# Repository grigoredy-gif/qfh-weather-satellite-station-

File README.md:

# QFH weather-satellite station: my own antenna and an all-discrete receiver

I'm Edy Grigore, an Electrical Engineering student at the University of
Twente. This is my personal project to receive weather satellites on 137 MHz
with hardware I designed myself: a QFH antenna and a radio receiver built only
from discrete parts (transistors, diodes, inductors and capacitors, no chips
in the signal path).

*Receiver version 2. This is a 3D picture that KiCad draws from the board file,
not a photo. The boards were ordered on 16 November 2026 and have not arrived
yet.*

Each section below starts with a short explanation that needs no radio
background. The numbers and the reasoning follow, with links to the detailed
pages. Words like "IF" or "image" are explained in
[Words used on this page](#words-used-on-this-page).

## Where the project stands (16 November 2026)

| Part | State |
|---|---|
| The antenna | designed with my own MATLAB tool, built and measured |
| Listening with a bought radio (SDR) | the Meteor-M satellite signal received and recognised; no picture decoded, because the signal was too weak |
| Receiver version 1 | designed, simulated and laid out; never ordered, because it was too expensive to have assembled |
| Receiver version 2 | designed, simulated block by block, laid out and checked. **Ordered on 16 November 2026: 5 boards, 2 of them assembled by JLCPCB. Not delivered yet, not tested, nothing measured** |

## Why I'm doing this

In my first year, the Module 4 project was to design an antenna and a
transmitter PCB. I really enjoyed that field, together with the High Frequency
Electronics, Electromagnetostatics and Electrodynamics courses, so I wanted to
go deeper: design my own antenna and my own receiver, and do the receiver fully
analog so I have to understand every stage at component level.

## How a weather picture reaches the ground

A weather satellite sends its pictures as a radio signal near 137 MHz. On the
ground the signal is extremely weak: around −90 to −100 dBm from my antenna,
which is less than a billionth of a milliwatt, or a few microvolts. The
receiver amplifies it to about a volt, filters out everything else, and turns
it into sound: a 2400 Hz tone whose loudness follows the brightness of the
picture, line by line. In my design an ESP32 microcontroller samples that
tone, and software on a PC turns it back into the picture (that firmware is
not written yet).

That is how the analog NOAA satellites worked (their "APT" signal). They were
switched off in 2025. The Meteor-M satellites that are still up send a digital
signal ("LRPT") that an analog FM receiver like mine cannot decode. So I test
the two halves separately: the antenna with a bought SDR on Meteor-M, and my
receiver on the bench, with a recorded NOAA pass played back into it by an
ADALM-Pluto SDR.

## The project in four parts

### 1. The antenna

A QFH (quadrifilar helix) antenna is two wire loops twisted around a mast. It
receives the circularly polarised signal of a satellite from almost anywhere
in the sky, so it does not need to be pointed. I wrote a MATLAB tool that
computes the antenna, exports it for simulation in NEC2, and prints a drilling
template for the mast. Then I built the antenna and measured it.

*Photo of my receiving setup in a park: the QFH antenna on its mast on a
concrete post, the ADALM-Pluto SDR (the blue box) and the laptop. The laptop
screen is edited in: it shows a SatDump screenshot from my own recording of
5 August 2026 (the spectrum and waterfall at 137.9 MHz). When the photo was
taken, the laptop showed a document.*

| The model (MATLAB) | The built antenna, measured |
|---|---|
|  |  |

*Left: the antenna as my MATLAB tool draws it (137.5 MHz, 1.78 mm wire).
Right: a measurement with a miniVNA Tiny (26 July 2026), S11 in dB in blue:
the best match is about −15 dB near 133 MHz and about −10 dB at 137.5 MHz.*

The built antenna resonates about 3 % lower than designed. For receiving, that
costs about 0.5 dB. **Deeper:** [`qfh_matlab/`](qfh_matlab) has the tool, the
4nec2 simulation next to this measurement, and why the plain design formulas
come out 2.2 % low in NEC2. The toolchain reproduces its reference program
exactly (all 127 NEC wire cards identical).

### 2. Listening with a bought SDR

Before building my own receiver, I recorded Meteor-M passes with the antenna
and an ADALM-Pluto. The signal is there (picture below), and SatDump's
decoder locked onto its error-correcting code, but no picture ever came out.

*Measurement: a real recording of Meteor-M N2-3 on 137.9 MHz, 6 August 2026,
shown by my `baseband_check.m`. Time runs upwards; the satellite's signal is
the band about 110 kHz wide in the middle.*

I first suspected the satellite. With help from the r/meteorsatellites
community I found the real cause: the mean signal-to-noise ratio was only
about 1.8 dB, below the 3 to 4 dB the decoder needs. The Pluto has no filter
and no low-noise amplifier at its input. **Deeper:**
[`lrpt_decoder/`](lrpt_decoder) (my own analysis chain, and the correction of
my first conclusion) and [`baseband_tools/`](baseband_tools) (tools that check
a recording before decoding it).

### 3. Receiver version 1: one conversion, coils wound by hand

The receiver is a superheterodyne. It mixes the 137.9 MHz signal with a
125 MHz signal made on the board, which shifts it down to 12.9 MHz (the
"intermediate frequency", IF). At 12.9 MHz it is much easier to amplify and
filter. Four amplifier stages give about 96 dB of gain there, a limiter cuts
the signal to a constant size, and a slope detector turns the frequency
changes into the 2400 Hz tone.

*Version 1, KiCad 3D picture (not a photo): 210 × 75 mm, 205 parts.*

I simulated every block in LTspice, then the whole receiver, and laid out the
board. It was checked many times. But building it needs 11 coils wound by hand
(7 on toroid cores, 4 air coils) and 11 trimmer capacitors that have to be
adjusted on the bench. JLCPCB quoted about €140 to assemble two boards. And
96 dB of gain at one frequency is easy to turn into an oscillator by
accident: the board had to grow to 210 mm with two shield fences across it.
I never ordered it.

**Deeper:** [`fm_receiver/`](fm_receiver) (the circuit and its 13
simulations) and [`pcb/`](pcb) (the board, every issue found and fixed).

### 4. Receiver version 2: two conversions, nothing to wind or tune

Version 2 does the same job, but it is designed for a factory. It has no coils
to wind and no trimmers to turn. JLCPCB places all 252 surface-mount parts by
machine and also solders the three connectors.

*Version 2 from above (KiCad 3D picture, not a photo): 100 × 100 mm. The
signal enters at the SMA jack at the top left, runs along the top edge, down
the right side, and back to the left through the second IF. The ESP32 DevKitC
plugs into the two socket rows at the bottom.*

Without trimmers, every tuned circuit has to be wide enough that normal part
tolerances cannot push it off the signal. At 12.9 MHz a filter that wide lets
through far too much noise. So version 2 converts the signal a second time,
from 12.9 MHz down to 1.418 MHz, where a filter of the right width (131 kHz)
is still tolerant enough. That second conversion is the central idea of
version 2. **Deeper:** [`fm_receiver_v2/`](fm_receiver_v2) and the board in
[`pcb_v2/`](pcb_v2).

## From version 1 to version 2

| | Version 1 | Version 2 |
|---|---|---|
| Conversions | one: 137.9 → 12.9 MHz | two: 137.9 → 12.9 → 1.418 MHz |
| Where the gain is | about 96 dB in one strip at 12.9 MHz | split between 12.9 MHz and 1.418 MHz |
| Coils | 11, wound by hand | 11 small SMD inductors, 3 values |
| Trimmers | 11, adjusted by hand | none |
| Oscillators | 25 MHz crystal × 5 = 125 MHz | the same, plus a 14.31818 MHz crystal |
| FM detector | slope detector (a tuned circuit) | charge-pump detector (no tuned circuit) |
| Supply | the ESP32 board's "5 V" pin (really about 4.6 V) | 3.3 V from a discrete regulator |
| Transistors | 20 | 38 |
| Parts | 205 | 252 surface-mount parts and 3 through-hole connectors |
| Board | 210 × 75 mm, 2 layers | 100 × 100 mm, 2 layers, all parts on the top |
| Assembly | by hand (JLCPCB quoted about €140 for 2 boards) | by JLCPCB: $39.99 (about €36) for 5 boards, 2 of them assembled |
| State | complete design, never ordered | ordered on 16 November 2026, not delivered yet |

The rule of the project stays the same: no ICs in the signal path. **Deeper:**
the reasons for each change are in
[`fm_receiver_v2/DESIGN_LOG.md`](fm_receiver_v2/DESIGN_LOG.md) ("Why a second
version" and "Frequency plan").

## Cost

**In short:** having two boards of version 1 assembled by JLCPCB was quoted at
about €140. Version 2 was ordered for $39.99 (about €36): five boards, two of
them assembled. The saving does not come from cheaper transistors. It comes
from designing the receiver around the way the factory charges.

| What | Price | Kind of figure | Source |
|---|---|---|---|
| Version 1, 2 boards assembled by JLCPCB (7 Nov 2026) | about €140 | JLCPCB quote | [`pcb/DESIGN_LOG.md`](pcb/DESIGN_LOG.md) |
| Version 2, first try with the wrong surface finish (OSP), 14 Nov | €143.52 for the assembly + €8.42 for the boards | JLCPCB quote | [`READ_ME_FIRST.txt`](pcb_v2/fabrication/READ_ME_FIRST.txt) |
| Version 2 without the connectors, my computation from JLCPCB's fee table, 14 Nov | $41.06 = €37.2 | computed | [`PARTS.md`](fm_receiver_v2/PARTS.md) |
| Version 2 in the cart, without the connectors: 5 boards, 2 assembled, HASL finish, 14 Nov | €3.62 + €30.37 = €33.99 | JLCPCB cart | [`COST.md`](fm_receiver_v2/COST.md) |
| **Version 2, ordered 16 Nov: 5 boards, 2 assembled with the connectors** | **$3.63 + $36.36 = $39.99 (about €36)** | **JLCPCB order list** | [`COST.md`](fm_receiver_v2/COST.md) |

All figures are without shipping, tax and the ESP32 board. The dollar figure is
about €36 at €1 = $1.1052.

Where the saving comes from:

1. **No coils to wind and no trimmers.** Every part comes from the factory's
   stock and is fitted there.
2. **The cheaper of JLCPCB's two assembly services ("Economic").** The dearer
   one ("Standard") charges for every different part type. A single part that
   JLCPCB marks "Standard only", or the wrong board finish, moves the whole
   order there. That is what happened to my first quote for version 2: the
   OSP finish made it €143.52 for the assembly alone. With the HASL finish the
   same files came to €30.37 in the cart.
3. **Parts from JLCPCB's fee-free lists.** 59 of the 63 part types are "Basic"
   or "Preferred" and carry no fee. Four are "Extended" at $3.07 each: the
   three inductor values and the 14.31818 MHz crystal.
4. **A small board** (100 × 100 mm, JLCPCB's cheapest size step) with every
   part on one side.

The three connectors (the SMA jack and the two socket rows) are through-hole
parts, which JLCPCB solders by hand for a fee. My computation said $12.70 more
for two boards, so at first I planned to solder them myself. The cart showed
about $6.60, so the order includes them.

**Deeper:** [`fm_receiver_v2/COST.md`](fm_receiver_v2/COST.md) has every
figure with its source, the price rules, and what did not get cheaper.

## What the version 2 simulations show

**In short:** before ordering anything, I simulated every block of version 2
in LTspice, then joined them up into the whole receiver, from the antenna to
the ESP32's pin. A simulation cannot prove that a board works, but it catches
mistakes that are cheap to fix on screen and expensive on a board. These are
the questions it answered. All of it is simulation: nothing of version 2 is
measured yet.

| Question | Simulated answer |
|---|---|
| Does each filter pass the satellite and block the "image" (a second frequency that would also come through the mixer)? | the first image (112.1 MHz) 38 dB down, the second (15.736 MHz) 42 dB down |
| Does it still work with normal part tolerances and nothing adjusted? | yes: in 300 runs with random part values, the narrow 1.418 MHz filter loses at most 2.1 dB, and the image stays at least 32 dB down (plot below). Only if every part is off in the same direction does the image come up to about 27 dB down |
| How weak a signal can it receive? | a clean picture from about −106 dBm, readable down to about −109 dBm |
| Does the level at the ESP32 depend on the signal strength? | no: the audio level stays the same from −121 dBm to −27 dBm at the input |
| Does a strong signal damage anything? | no: the Pluto at full power with no attenuator stays inside every limit of the input transistor |
| Do the crystal oscillators start, and are they gentle on the crystals? | yes, also with the worst crystal the data sheet allows; 56 to 75 µW into crystals rated for at most 200 µW |
| Can the strip of amplifiers oscillate by itself through stray coupling? | the simulations found how little coupling is too much (as little as 0.005 pF in one place); those limits became layout rules, and the strays computed from the finished copper are 70 to 3000 times smaller |
| Does the picture survive? | yes: a 2400 Hz tone with the picture in its loudness comes through with its depth only 1.4 % low |
| How much power? | the whole receiver draws 37 mA |

*Simulation (LTspice), not a measurement. The three filter sections of version
2: black with nominal parts, grey for 300 runs with random part values inside
their tolerance, dashed for all parts at the bottom or at the top of their
tolerance at once. Each curve is shown relative to the nominal response at the
signal. Made with
[`fm_receiver_v2/plots/plot_filter_tolerance.m`](fm_receiver_v2/plots/plot_filter_tolerance.m)
from the decks `rx2_a1`, `a2`, `d1`, `d2`, `f1` and `f3`.*

The simulations also caught several mistakes before any copper existed, for
example a simulator default that made a crystal oscillator look ten times
gentler than it is, and two bypass capacitors that resonated right in the
satellite band. **Deeper:** [`fm_receiver_v2/README.md`](fm_receiver_v2/README.md)
has the results block by block and "Things the simulation caught";
[`fm_receiver_v2/DESIGN_LOG.md`](fm_receiver_v2/DESIGN_LOG.md) has every number
with the test deck that produced it.

## What is checked, and what is not

- **Checked:** every block and the whole chain in simulation, including part
  tolerances, the supply range (3.0 to 3.6 V), a slow transistor model and the
  board's stray capacitances. The schematic is generated from the simulated
  circuit by a script, and a second script proves that both are the same
  circuit. The board passes KiCad's design-rule check.
- **Reviewed:** in four rounds (13 to 15 November 2026) by independent AI
  review agents. The first round found three risks in the circuit, and the
  second found a wrong rotation for the transistors in the factory's placement
  file; all were fixed. The last two rounds found no fault. JLCPCB's own
  placement preview of the final files without the connectors was checked as
  well: every transistor, diode and crystal sits the right way round on its
  pads.
- **Changed after the reviews:** four mounting holes, and the first 4 mm of
  the antenna track moved to the bottom side under the SMA jack. These were
  checked by script (rules check, a comparison with the reviewed board, the
  factory files read back), but no reviewer saw them. The same holds for the
  placement files with the three connectors, which the order uses: a script
  checks their places against JLCPCB's own footprints.
- **Simulated only:** every performance figure of version 2. Transistor
  models, inductor quality factors, crystal data and stray capacitances are
  estimates from data sheets and calculations.
- **Not done:** the boards have not arrived, so nothing of version 2 is tested
  or measured. No firmware is written. The final checks used no temperature corners.
- **The risks I expect on the bench:** an oscillation through stray coupling
  on the real copper; the 12.9 MHz filter landing too low if many parts are
  off the same way (in the worst case the checks found, the receiver would
  need about 30 dB more signal; with nominal parts it loses 1.7 dB), which is
  fixed by changing a few capacitors; and the start-up margin of the 25 MHz
  oscillator in the worst case (1.5 times). Each tuned circuit has a spare
  capacitor pad for corrections.

## What comes next

1. **When the boards arrive** (ordered on 16 November 2026): check that my
   ESP32 DevKitC fits the soldered sockets (the board assumes 25.40 mm between
   its two pin rows).
2. **Bring-up on the bench, one block at a time:** supply and stage currents,
   then the two oscillators, then a 137.9 MHz carrier from the Pluto, then an
   FM signal with a 2400 Hz tone, then a recorded satellite pass.
3. **Firmware for the ESP32:** sample the audio continuously (at least
   20,000 samples per second), send it to the PC, and decode the picture.
4. **On the reception side:** an LNA and a 137 MHz SAW filter in front of the
   SDR, then another try at Meteor-M.
5. **Later:** close the loop with my own hardware on both ends: a second QFH
   antenna and an FM transmitter on my own PCB, on a frequency I'm allowed to
   transmit on.

## What's in here

| Folder | What it is | State |
|---|---|---|
| [`qfh_matlab`](qfh_matlab) | MATLAB toolchain that designs the QFH antenna, exports it to NEC2 and prints a drilling template | antenna designed, simulated, built and measured |
| [`fm_receiver`](fm_receiver) | receiver version 1 and its LTspice simulations, block by block up to the full chain | simulated from RF input to the ADC |
| [`pcb`](pcb) | the KiCad board of version 1 | finished design, never ordered |
| [`fm_receiver_v2`](fm_receiver_v2) | receiver version 2: 11 circuit blocks, 32 test decks, the parts list and the cost | simulated from the antenna to the ADC |
| [`pcb_v2`](pcb_v2) | the KiCad schematic and board of version 2, generated by scripts, and the files for JLCPCB | ordered on 16 November 2026, not delivered yet |
| [`lrpt_decoder`](lrpt_decoder) | my own MATLAB analysis chain for Meteor-M LRPT recordings | working; taught me my signal was too weak |
| [`baseband_tools`](baseband_tools) | tools to check an SDR recording before decoding it | working |

## Tools

LTspice, KiCad 10 (with Python scripts and Freerouting), MATLAB R2025a,
4nec2 / NEC2, SatDump, an ADALM-Pluto SDR and a miniVNA Tiny.

## Words used on this page

- **dBm:** signal power compared with 1 milliwatt, in decibels. 0 dBm is
  1 mW, −30 dBm is 1 µW, −100 dBm is 0.1 picowatt. Every 10 dB is a factor of 10.
- **SDR (software-defined radio):** a receiver that turns the radio signal into
  numbers early and does the rest in software. I use an ADALM-Pluto.
- **Superheterodyne:** a receiver that first shifts the signal to a fixed, lower
  frequency, where it is easier to amplify and filter.
- **LO (local oscillator):** the signal made on the board that does that shift.
- **IF (intermediate frequency):** the lower frequency the signal is shifted
  to: 12.9 MHz in both versions, and 1.418 MHz as well in version 2.
- **Image:** a second input frequency that a mixer shifts to the same IF as
  the wanted one. A filter in front of the mixer has to block it.
- **Tuned circuit:** an inductor and a capacitor that together pass one
  frequency band. A **trimmer** is a capacitor that you adjust with a
  screwdriver to put that band in the right place.
- **Basic, Preferred, Extended:** JLCPCB's classes of parts. Extended parts
  cost an extra fee per part type.
- **Simulation, measurement, 3D picture:** every picture here says which one it
  is. A 3D picture is drawn by KiCad from the design files; it is not a photo.

## Credits and license

This is my project. I set the goals and made or approved every decision. I
used Claude (Anthropic) as an AI assistant along the way; each folder's README
says what it helped with. The antenna code is a MATLAB port of John Coppens'
online QFH calculator and of QFH2nec, both GPL-licensed, so `qfh_matlab` is
GPL-3.0. Everything else is MIT licensed (see [LICENSE](LICENSE)).

Edy Grigore

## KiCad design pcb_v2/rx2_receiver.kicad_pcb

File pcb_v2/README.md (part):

# Schematic and board of receiver version 2

The KiCad 10 schematic of the version 2 receiver. It is not drawn by hand. A
script builds it from the eleven circuit blocks in
[`../fm_receiver_v2/simulations/`](../fm_receiver_v2/simulations) and from the
parts list [`rx2_parts.csv`](../fm_receiver_v2/rx2_parts.csv). A second script
then checks that the result is the simulated circuit. The board is laid out by
scripts as well. It passes KiCad's design rules check and has been checked by
several AI reviewers (see the table). The files for JLCPCB are written.
It was ordered from JLCPCB on 2026-11-16 (5 boards, 2 of them assembled, the
connectors included). The boards have not arrived, and nothing is tested on a
bench.

*KiCad 3D picture of the board, not a photo. It is drawn with the SMA jack and
the two socket rows fitted, which JLCPCB solders by hand; the 11 spare capacitor
positions are empty, and the ESP32 DevKitC is not drawn.*

## State (2026-11-16)

| | |
|---|---|
| Symbols | 266: the 252 parts of the parts list, 3 connectors, 11 spare capacitor positions (not fitted) |
| Electrical rules check (kicad-cli 10.0.3, all severities) | 0 errors, 0 warnings |
| Comparison with the blocks | 0 differences: 578 pins, 117 nodes in the blocks = 117 nets in the schematic |
| Value, footprint, LCSC number | equal to `rx2_parts.csv` for all 252 parts |
| Board | 100 × 100 mm, 2 layers, 273 footprints (the 266 of the schematic, 3 fiducial marks and 4 mounting holes), all on the top side |
| Design rules check of the board (kicad-cli, all severities, with schematic parity) | 0 errors, 0 warnings, 0 open connections, 0 differences to the schematic |
| Copper on the bottom layer | ground, and five short tracks (38.5 mm in all): four hops, and the first 4.25 mm of the antenna track under the SMA jack. None is under the tuned circuits of an IF strip. One (11.7 mm, supply) runs under the track from mixer 1 to the first tuned circuit of the first IF |
| Second check of the board (2026-11-14) | by two AI agents that were not given my reasoning: pin orders against the makers' data sheets, footprints, the DevKitC sockets, the layout rules measured on the board, JLCPCB's limits. No fault found on the board. The check found that JLCPCB needs turned angles for the SOT-23 parts in the placement file; `gen/rx2_fab.py` now writes them |
| Last check before the order (2026-11-15) | by three AI agents, each from one side and none given my reasoning: the circuit and its simulations (both crystal oscillators with the worst crystal the data sheet allows, the chain with the board's strays and the real part values), the parts and pins (their own comparison of the blocks with the board pads: 0 differences on 551 pins), the board and the JLCPCB files (the zip equals a fresh export, their own connectivity test). No fault found. I repeated their key results. The board is still not tested on a bench |
| Third review (2026-11-15) | by three more AI agents: the application and the circuit (the signal through every filter, noise, the signal generator and the ESP32); what gets built (the Gerber and drill files read by the reviewer's own parser: every pad and hole is right, and a netlist taken from those files alone has no short and no open; the footprints against the makers' drawings); the board as hardware (stray capacitances solved numerically from the real copper: each one 70 to 3000 times under its limit, all together a margin of 10 to 30 against the self-lock of the second IF). No fault found. One thing to mind when soldering: the antenna track ran under the metal base of the SMA jack, with only solder mask between (changed afterwards, see the next row) |
| Two changes after the reviews (2026-11-15) | **Mounting holes:** four holes of 3.2 mm for M3 screws, not plated, on a rectangle of 92.0 × 86.0 mm. To make room, the corner of the 3.3 V supply track at the top right became a diagonal, two fiducial marks and one silkscreen text moved, and two ground vias were added. **Antenna track:** it now leaves the SMA jack on the bottom side and comes up through a via beside the jack, so only ground copper lies under the jack's metal base. **Checked afterwards:** a script compared the changed board with the reviewed one, item by item (footprints, pads, tracks, vias, texts, pour outlines, nets): nothing else differs. The rules check is clean again. The new Gerber and drill files were read with the parser of the earlier review: every pad and hole is right, and a netlist taken from the files alone has no short and no open. The AI reviewers have not seen these two changes |
| Files for JLCPCB (`fabrication/`) | Gerber zip (one drill file for the plated holes, one for the four mounting holes), and two pairs of BOM and placement file: the 252 surface-mount parts alone (63 lines), or with the SMA jack and the two DevKitC sockets as well (65 lines, 255 parts). For each part, JLCPCB's own footprint at the written place and angle lands on the board's pads (largest difference 0.30 mm). The first pair is byte for byte the pair that was reviewed |
| Order (2026-11-16) | placed at JLCPCB: 5 boards (green, 1.6 mm, HASL with lead), 2 of them assembled in economic assembly on the top side. Files: the Gerber zip and the second pair (`rx2_receiver_jlc_bom_with_connectors.csv`, `rx2_receiver_jlc_cpl_with_connectors.csv`), so JLCPCB also solders the SMA jack and the two sockets by hand. The uploaded files are byte for byte the ones in `fabrication/`. JLCPCB's order list: $3.63 for the boards and $36.36 for the assembly, without shipping and tax ([`../fm_receiver_v2/COST.md`](../fm_receiver_v2/COST.md)). `fabrication/READ_ME_FIRST.txt` still describes the choice of pair as open |
| JLCPCB's placement preview of the final files | checked for the pair without the connectors: every transistor, diode and crystal with pin 1 on pad 1, the four holes present, no top-side track under the SMA jack. A look at the connectors in the preview of the ordered pair is not recorded; `gen/rx2_fab.py` checks their places against JLCPCB's footprints |

## How to read it

- Open `rx2_receiver.kicad_pro` in KiCad 10, or read `rx2_receiver.pdf`.
- The root sheet shows the eleven blocks and the layout rules. Each block has
  its own sheet, in the order of the signal.
- Parts are not joined by drawn wires. Every pin has a short wire with a net
  name, and pins with the same name are connected. The names are the node
  names of the simulation, so a net can be looked up in the block file.
- Nets that go from one sheet to another have a global label: `m1in`, `osc25`,
  `lo1`, `t1`, `m2in`, `lo2`, `t5`, `det`, `adc`, `vb`, `vbd`. Ground and the
  3.3 V rail are the power symbols `GND` and `VCC`.
- Under each value stands the part's name in the simulation (field `Sim`).
  The other fields are `LCSC`, `MPN` and `Assembly` (JLCPCB, by hand, not
  fitted).
- The comments of the block files and the layout rules for the board are
  printed on the sheets.

## Sheets and reference numbers

A reference is a letter, then the sheet number times 100 plus a running
number in the order of the block file: `R101` is the first resistor of sheet
1, `Q1101` the first transistor of sheet 11.
[`rx2_refs.csv`](rx2_refs.csv) lists every simulation name with its reference.

| Sheet | Block file | Content |
|---|---|---|
| 1 | `rx2_blk_fe.inc` | front end at 137.9 MHz, antenna connector |
| 2 | `rx2_blk_lo1osc.inc` | 25 MHz crystal oscillator |
| 3 | `rx2_blk_lo1mul.inc` | multiplier to 125 MHz |
| 4 | `rx2_blk_mix1.inc` | mixer 1 |
| 5 | `rx2_blk_if1.inc` | first IF, 12.9 MHz |
| 6 | `rx2_blk_lo2.inc` | 14.318 MHz crystal oscillator |
| 7 | `rx2_blk_mix2.inc` | mixer 2 |
| 8 | `rx2_blk_if2.inc` | second IF at 1.418 MHz, limiter, detector |
| 9 | `rx2_blk_audio.inc` | audio chain to the ADC pin |
| 10 | `rx2_blk_reg.inc` | 3.3 V regulator, sockets for the ESP32 DevKitC |
| 11 | `rx2_blk_bias.inc` | the two bias references |

## Part types: symbol, footprint, pins

| Part | KiCad symbol | KiCad footprint | Pins |
|---|---|---|---|
| Resistor 0603 | `Device:R` | `Resistor_SMD:R_0603_1608Metric` | no direction |
| Capacitor 0603 | `Device:C` | `Capacitor_SMD:C_0603_1608Metric` | no direction |
| Capacitor 100 µF, 1206 | `Device:C` | `Capacitor_SMD:C_1206_3216Metric` | no direction |
| Inductor 68 nH, 0603 | `Device:L` | `rx2:L_0603_LQW18A` | no direction |
| Inductor 3.3 µH, 1008 | `Device:L` | `rx2:L_1008_AHW2520C` | no direction |
| Inductor 100 µH, 1210 | `Device:L` | `rx2:L_1210_NLV32` | no direction |
| 2SC3356, S9018, MMBT3904 | `Transistor_BJT:Q_NPN_BEC` | `Package_TO_SOT_SMD:SOT-23` | 1 base, 2 emitter, 3 collector |
| MMBT3906 | `Transistor_BJT:Q_PNP_BEC` | `Package_TO_SOT_SMD:SOT-23` | 1 base, 2 emitter, 3 collector |
| BAS70 | `rx2:D_Schottky_A1_K3` (in `rx2.kicad_sym`) | `Package_TO_SOT_SMD:SOT-23` | 1 anode, 3 cathode, 2 free |
| BAV99 | `Device:D_Dual_Series_AKC` | `Package_TO_SOT_SMD:SOT-23` | 3 to the signal node, 1 and 2 to ground |
| Crystal 3225 | `Device:Crystal_GND24` | `Crystal:Crystal_SMD_3225-4Pin_3.2x2.5mm` | 1 and 3 crystal, 2 and 4 ground |

In the block files a transistor line lists collector, base, emitter. The
generator puts them on pins 3, 1, 2. The footprint `SOT-23` has pads 1 and 2
on one side and pad 3 alone on the other, which is the usual numbering.

## Parts that are not in the simulation

| Part | Reference | State |
|---|---|---|
| Antenna connector, SMA, LCSC C496549 | `J101` | its data sheet shows a vertical through-hole jack (the coax plugs in from above), not an edge type. Footprint `rx2:SMA_BWSMA-KE-Z001_Vertical`: five holes of 1.4 mm, four legs on a 5.08 mm square. Soldered by JLCPCB (the order of 2026-11-16 uses the second pair of order files) |
| Two 1×19 sockets for the DevKitC, LCSC C2932678 | `J1001`, `J1002` | soldered by JLCPCB (second pair of order files). Pins used, copied from the version 1 board: left row (J2) 1 = 3V3, 3 = GPIO36, 14 = GND, 19 = 5V; right row (J3) 1 and 7 = GND. Confirmed in Espressif's pin table. The rows are 25.40 mm apart as on Espressif's drawing; some clone boards are narrower, so check the DevKitC against the sockets when the boards arrive |
| Spare capacitor positions | 11 capacitors with the value `spare` | empty 0603 footprints, marked do-not-populate and left out of the BOM. One per tuned circuit, across the same two nodes as its small tuning capacitor (or across the inductor where there is none) |

Test points are not in the schematic. They are decided with the board.

## What is checked and what is not

**Checked by script** (`gen/rx2_check.py`, which reads the block files with its
own code, not with the generator's):

- every part of the blocks is exactly one symbol, and the other way round;
- every value: the text against the parts list, the number or the type against
  the block file;
- the connections: the nets of the schematic and the nodes of the blocks split
  the 578 pins into the same 117 groups. Before the comparison the layout
  estimates of the blocks (names ending in `_x`) are taken out: an estimated
  capacitor is dropped, an estimated inductor is a short, and a package model
  around a transistor is replaced by the transistor's three pins;
- footprint and LCSC number of every part against the parts list;
- the connectors and the spare positions against a table in the script.

**Checked by KiCad:** the electrical rules check, with no errors and no
warnings.

**Read in the data sheets of the exact LCSC parts** (2026-11-14): S9018
(C41375130), MMBT3904 (C20526) and MMBT3906 (C7420354) have pin 1 base, pin 2
emitter, pin 3 collector, with pin 3 alone on its side of the package. That is
the pad numbering of the `SOT-23` footprint. The 2SC3356, the BAS70, the BAV99
and the crystals were read for the parts list
([`PARTS.md`](../fm_receiver_v2/PARTS.md)).

**Not checked yet:**

- The land patterns of the crystals, the three inductors, the SMA jack and the sockets were read in the
  data sheets. KiCad's inductor footprints did not match, so the three inductors and the SMA jack have
  their own footprints in `rx2.pretty`. Not in the data sheets: the pad diameter for the SMA jack (only
  the hole size is given) and whether the 100 µH inductor is shielded (I treat it as open).
- The board is checked by KiCad's rules, by me in pictures, and by AI agents in three rounds (see the
  table at the top). The mounting holes and the moved antenna track came after those rounds and are
  checked by script only. The board is not checked by another person and not on a bench. The stray
  capacitances on the board are estimates and numerical calculations from the copper, not
  measurements. The coupling limits behind the layout rules come from simulation.
- The drawing shows connections by name only. It was not checked by eye part
  by part; the script check above stands in for that.

## The board

100 × 100 mm, 2 layers, 1.6 mm. Every part is on the top side. The bottom side is
a ground plane with five short tracks on it. [`preview/board_top.png`](preview/board_top.png)
and [`preview/board_bottom.png`](preview/board_bottom.png) show both sides.

**Where the blocks are.** The antenna jack is at the top left. The front end and
mixer 1 run along the top edge. The first IF is a column down the right edge, with
mixer 2 below it. The second IF is a row that runs from mixer 2 to the left, with
the detector at its left end and the audio chain beyond it. The ESP32 DevKitC
plugs in along the bottom edge, USB at the left edge; the regulator sits under
it. The 25 MHz oscillator and the multiplier are in the middle, the second
oscillator at the bottom right.

**Why like this.** The design log has eight layout rules
([`DESIGN_LOG.md`](../fm_receiver_v2/DESIGN_LOG.md), sections "Layout rules that
came out of this" and "Found while laying out the board"). The two that shaped
the board most: the pump driver at the end of the second IF must be far from the
first IF, and far from the first tuned circuit of the second IF. Measured on
the board from copper to copper (`gen/rx2_measure.py`): the pump driver's
output node is 52.6 mm from the nearest tuned node of the first IF and 30.8 mm
from the first tuned node of the second IF. Its emitter and base nodes
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
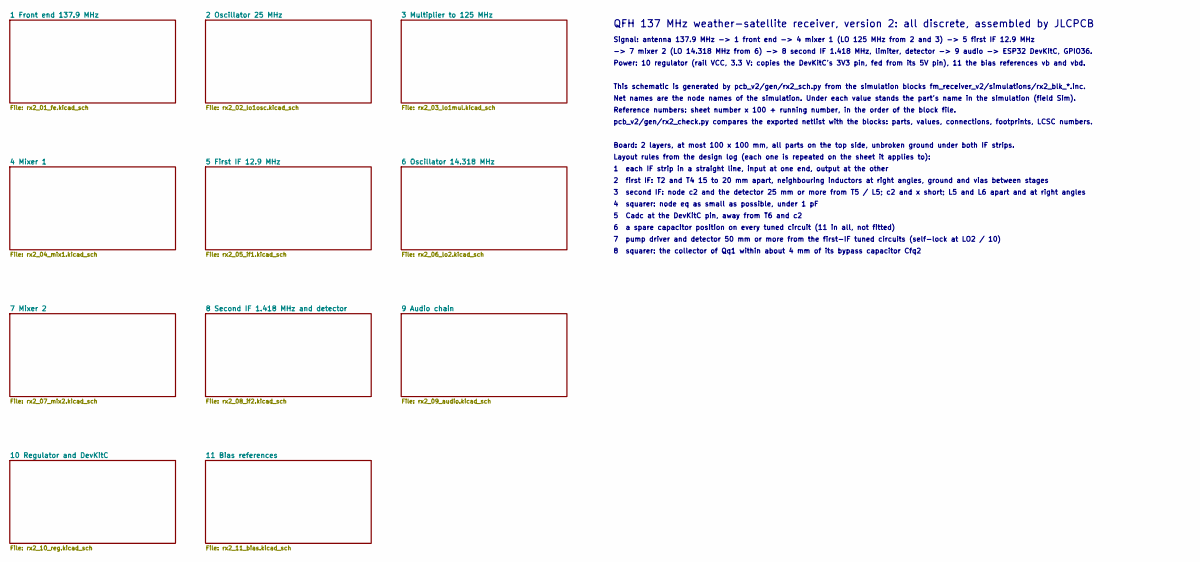
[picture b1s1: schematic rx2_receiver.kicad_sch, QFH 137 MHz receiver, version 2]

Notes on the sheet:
QFH 137 MHz weather-satellite receiver, version 2: all discrete, assembled by JLCPCB
Signal: antenna 137.9 MHz -> 1 front end -> 4 mixer 1 (LO 125 MHz from 2 and 3) -> 5 first IF 12.9 MHz
-> 7 mixer 2 (LO 14.318 MHz from 6) -> 8 second IF 1.418 MHz, limiter, detector -> 9 audio -> ESP32 DevKitC, GPIO36.
Power: 10 regulator (rail VCC, 3.3 V: copies the DevKitC's 3V3 pin, fed from its 5V pin), 11 the bias references vb and vbd.
This schematic is generated by pcb_v2/gen/rx2_sch.py from the simulation blocks fm_receiver_v2/simulations/rx2_blk_*.inc.
Net names are the node names of the simulation. Under each value stands the part's name in the simulation (field Sim).
Reference numbers: sheet number x 100 + running number, in the order of the block file.
pcb_v2/gen/rx2_check.py compares the exported netlist with the blocks: parts, values, connections, footprints, LCSC numbers.
Board: 2 layers, at most 100 x 100 mm, all parts on the top side, unbroken ground under both IF strips.
Layout rules from the design log (each one is repeated on the sheet it applies to):
1 each IF strip in a straight line, input at one end, output at the other
2 first IF: T2 and T4 15 to 20 mm apart, neighbouring inductors at right angles, ground and vias between stages
3 second IF: node c2 and the detector 25 mm or more from T5 / L5; c2 and x short; L5 and L6 apart and at right angles
4 squarer: node eq as small as possible, under 1 pF
5 Cadc at the DevKitC pin, away from T6 and c2
6 a spare capacitor position on every tuned circuit (11 in all, not fitted)
7 pump driver and detector 50 mm or more from the first-IF tuned circuits (self-lock at LO2 / 10)
8 squarer: the collector of Qq1 within about 4 mm of its bypass capacitor Cfq2

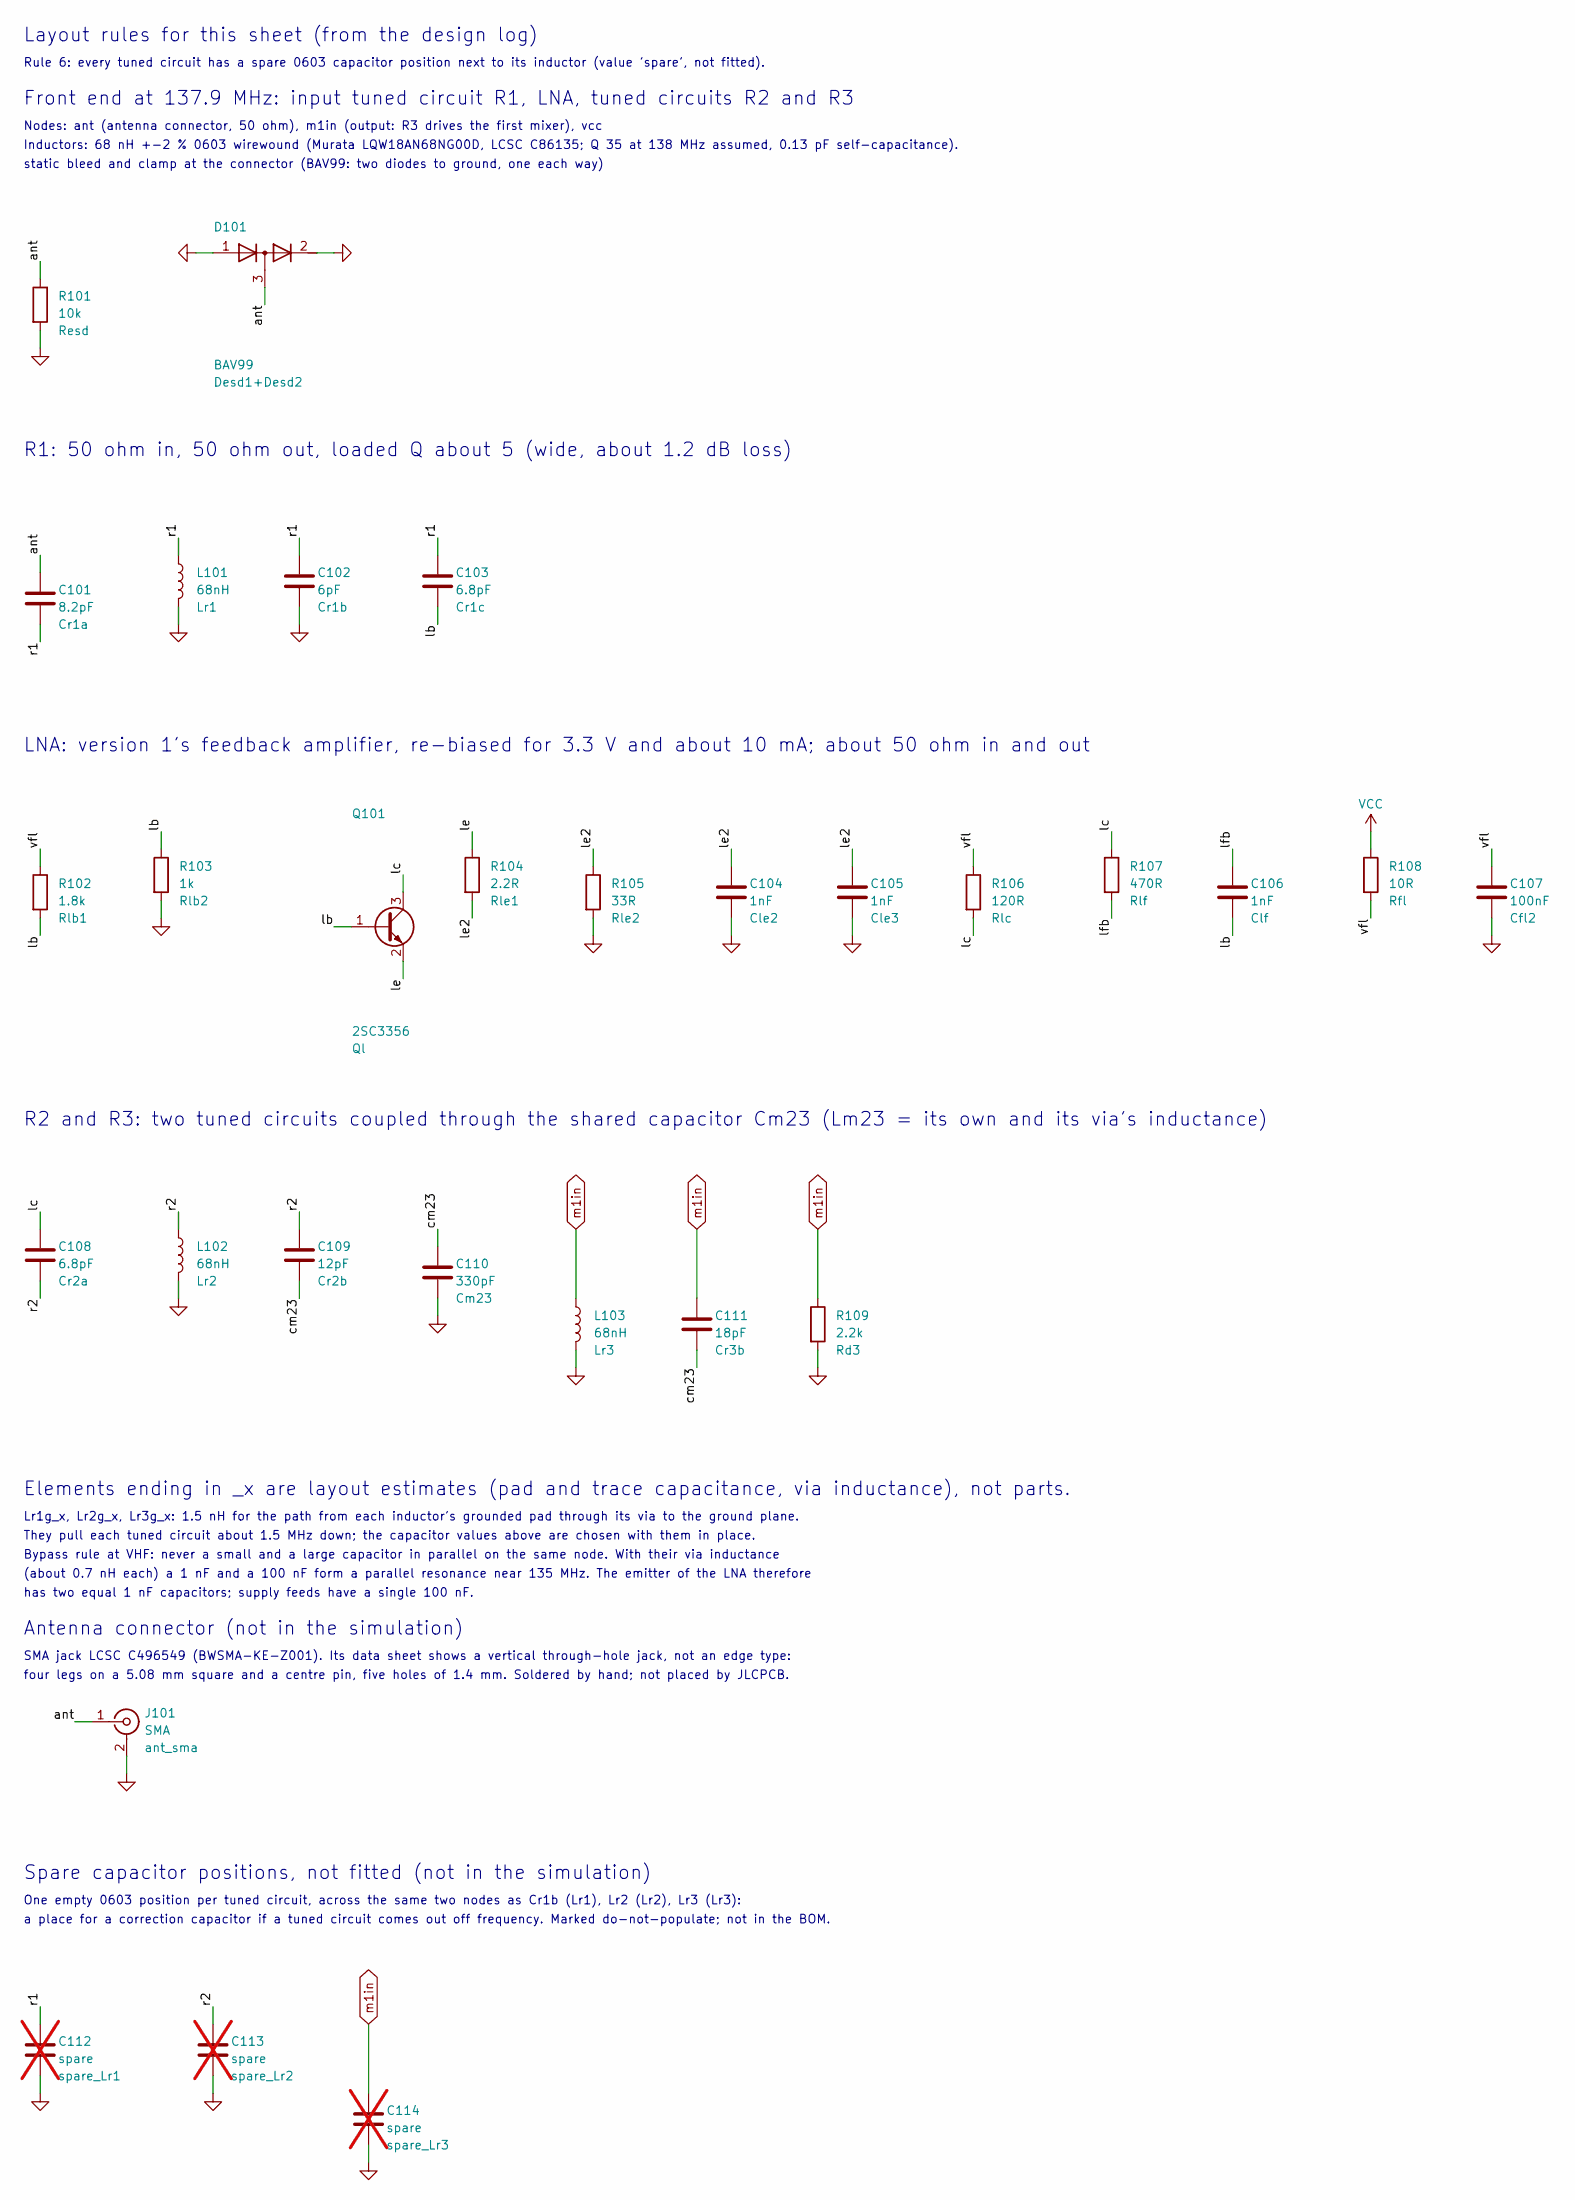
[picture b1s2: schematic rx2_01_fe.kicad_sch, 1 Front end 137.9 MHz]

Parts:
C101: 8.2pF; C_0603_1608Metric; MPN 0603CG8R2C500NT; LCSC C1685
C102: 6pF; C_0603_1608Metric; MPN 0603CG6R0C500NT; LCSC C37474
C103, C108: 6.8pF; C_0603_1608Metric; MPN 0603CG6R8C500NT; LCSC C1679
C104, C105, C106: 1nF; C_0603_1608Metric; MPN CL10B102KB8NNNC; LCSC C1588
C107: 100nF; C_0603_1608Metric; MPN CC0603KRX7R9BB104; LCSC C14663
C109: 12pF; C_0603_1608Metric; MPN CL10C120JB8NNNC; LCSC C38523
C110: 330pF; C_0603_1608Metric; MPN CL10C331JB8NNNC; LCSC C1664
C111: 18pF; C_0603_1608Metric; MPN CL10C180JB8NNNC; LCSC C1647
C112, C113, C114: spare; C_0603_1608Metric; not fitted
D101: BAV99; SOT-23; MPN BAV99,215; LCSC C2500
J101: SMA; SMA_BWSMA-KE-Z001_Vertical; MPN BWSMA-KE-Z001; LCSC C496549
L101, L102, L103: 68nH; L_0603_LQW18A; MPN LQW18AN68NG00D; LCSC C86135
Q101: 2SC3356; SOT-23; MPN 2SC3356; LCSC C28646266
R101: 10k; R_0603_1608Metric; MPN 0603WAF1002T5E; LCSC C25804
R102: 1.8k; R_0603_1608Metric; MPN 0603WAF1801T5E; LCSC C4177
R103: 1k; R_0603_1608Metric; MPN 0603WAF1001T5E; LCSC C21190
R104: 2.2R; R_0603_1608Metric; MPN 0603WAF220KT5E; LCSC C22939
R105: 33R; R_0603_1608Metric; MPN 0603WAF330JT5E; LCSC C23140
R106: 120R; R_0603_1608Metric; MPN 0603WAF1200T5E; LCSC C22787
R107: 470R; R_0603_1608Metric; MPN 0603WAF4700T5E; LCSC C23179
R108: 10R; R_0603_1608Metric; MPN 0603WAF100JT5E; LCSC C22859
R109: 2.2k; R_0603_1608Metric; MPN 0603WAF2201T5E; LCSC C4190

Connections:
/1 Front end 137.9 MHz/ant: C101.1, D101.3 (common), J101.1 (In), R101.1
/1 Front end 137.9 MHz/cm23: C109.2, C110.1, C111.2
/1 Front end 137.9 MHz/lb: C103.2, C106.2, Q101.1 (B), R102.2, R103.1
/1 Front end 137.9 MHz/lc: C108.1, Q101.3 (C), R106.2, R107.1
/1 Front end 137.9 MHz/le: Q101.2 (E), R104.1
/1 Front end 137.9 MHz/le2: C104.1, C105.1, R104.2, R105.1
/1 Front end 137.9 MHz/lfb: C106.1, R107.2
/1 Front end 137.9 MHz/r1: C101.2, C102.1, C103.1, C112.1, L101.1
/1 Front end 137.9 MHz/r2: C108.2, C109.1, C113.1, L102.1
/1 Front end 137.9 MHz/vfl: C107.1, R102.1, R106.1, R108.2
GND: C102.2, C104.2, C105.2, C107.2, C110.2, C112.2, C113.2, C114.2, D101.1 (A), D101.2 (K), J101.2 (Ext), L101.2, L102.2, L103.2, R101.2, R103.2, R105.2, R109.2; also elsewhere on the board
VCC: R108.1; also elsewhere on the board
m1in: C111.1, C114.1, L103.1, R109.1; also elsewhere on the board

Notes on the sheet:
Layout rules for this sheet (from the design log)
Rule 6: every tuned circuit has a spare 0603 capacitor position next to its inductor (value 'spare', not fitted).
Front end at 137.9 MHz: input tuned circuit R1, LNA, tuned circuits R2 and R3
Nodes: ant (antenna connector, 50 ohm), m1in (output: R3 drives the first mixer), vcc
Inductors: 68 nH +-2 % 0603 wirewound (Murata LQW18AN68NG00D, LCSC C86135; Q 35 at 138 MHz assumed, 0.13 pF self-capacitance).
static bleed and clamp at the connector (BAV99: two diodes to ground, one each way)
R1: 50 ohm in, 50 ohm out, loaded Q about 5 (wide, about 1.2 dB loss)
LNA: version 1's feedback amplifier, re-biased for 3.3 V and about 10 mA; about 50 ohm in and out
R2 and R3: two tuned circuits coupled through the shared capacitor Cm23 (Lm23 = its own and its via's inductance)
Elements ending in _x are layout estimates (pad and trace capacitance, via inductance), not parts.
Lr1g_x, Lr2g_x, Lr3g_x: 1.5 nH for the path from each inductor's grounded pad through its via to the ground plane.
They pull each tuned circuit about 1.5 MHz down; the capacitor values above are chosen with them in place.
Bypass rule at VHF: never a small and a large capacitor in parallel on the same node. With their via inductance
(about 0.7 nH each) a 1 nF and a 100 nF form a parallel resonance near 135 MHz. The emitter of the LNA therefore
has two equal 1 nF capacitors; supply feeds have a single 100 nF.
Antenna connector (not in the simulation)
SMA jack LCSC C496549 (BWSMA-KE-Z001). Its data sheet shows a vertical through-hole jack, not an edge type:
four legs on a 5.08 mm square and a centre pin, five holes of 1.4 mm. Soldered by hand; not placed by JLCPCB.
Spare capacitor positions, not fitted (not in the simulation)
One empty 0603 position per tuned circuit, across the same two nodes as Cr1b (Lr1), Lr2 (Lr2), Lr3 (Lr3):
a place for a correction capacitor if a tuned circuit comes out off frequency. Marked do-not-populate; not in the BOM.

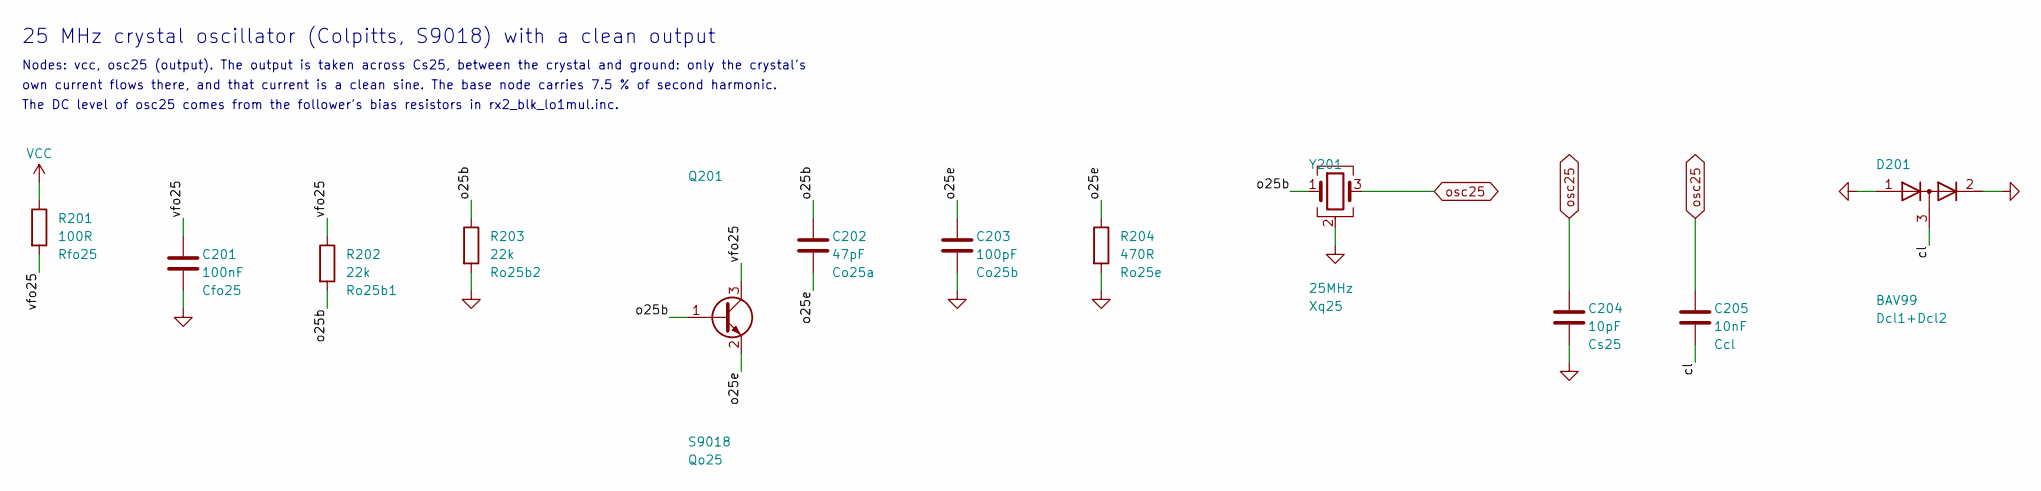
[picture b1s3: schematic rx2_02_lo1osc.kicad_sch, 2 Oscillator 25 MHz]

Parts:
C201: 100nF; C_0603_1608Metric; MPN CC0603KRX7R9BB104; LCSC C14663
C202: 47pF; C_0603_1608Metric; MPN CL10C470JB8NNNC; LCSC C1671
C203: 100pF; C_0603_1608Metric; MPN CL10C101JB8NNNC; LCSC C14858
C204: 10pF; C_0603_1608Metric; MPN CL10C100JB8NNNC; LCSC C1634
C205: 10nF; C_0603_1608Metric; MPN 0603B103K500NT; LCSC C57112
D201: BAV99; SOT-23; MPN BAV99,215; LCSC C2500
Q201: S9018; SOT-23; MPN S9018; LCSC C41375130
R201: 100R; R_0603_1608Metric; MPN 0603WAF1000T5E; LCSC C22775
R202, R203: 22k; R_0603_1608Metric; MPN 0603WAF2202T5E; LCSC C31850
R204: 470R; R_0603_1608Metric; MPN 0603WAF4700T5E; LCSC C23179
Y201: 25MHz; Crystal_SMD_3225-4Pin_3.2x2.5mm; MPN X322525MOB4SI; LCSC C9006

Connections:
/2 Oscillator 25 MHz/cl: C205.2, D201.3 (common)
/2 Oscillator 25 MHz/o25b: C202.1, Q201.1 (B), R202.2, R203.1, Y201.1
/2 Oscillator 25 MHz/o25e: C202.2, C203.1, Q201.2 (E), R204.1
/2 Oscillator 25 MHz/vfo25: C201.1, Q201.3 (C), R201.2, R202.1
GND: C201.2, C203.2, C204.2, D201.1 (A), D201.2 (K), R203.2, R204.2, Y201.2 (G), Y201.4 (G); also elsewhere on the board
VCC: R201.1; also elsewhere on the board
osc25: C204.1, C205.1, Y201.3; also elsewhere on the board

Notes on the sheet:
25 MHz crystal oscillator (Colpitts, S9018) with a clean output
Nodes: vcc, osc25 (output). The output is taken across Cs25, between the crystal and ground: only the crystal's
own current flows there, and that current is a clean sine. The base node carries 7.5 % of second harmonic.
The DC level of osc25 comes from the follower's bias resistors in rx2_blk_lo1mul.inc.

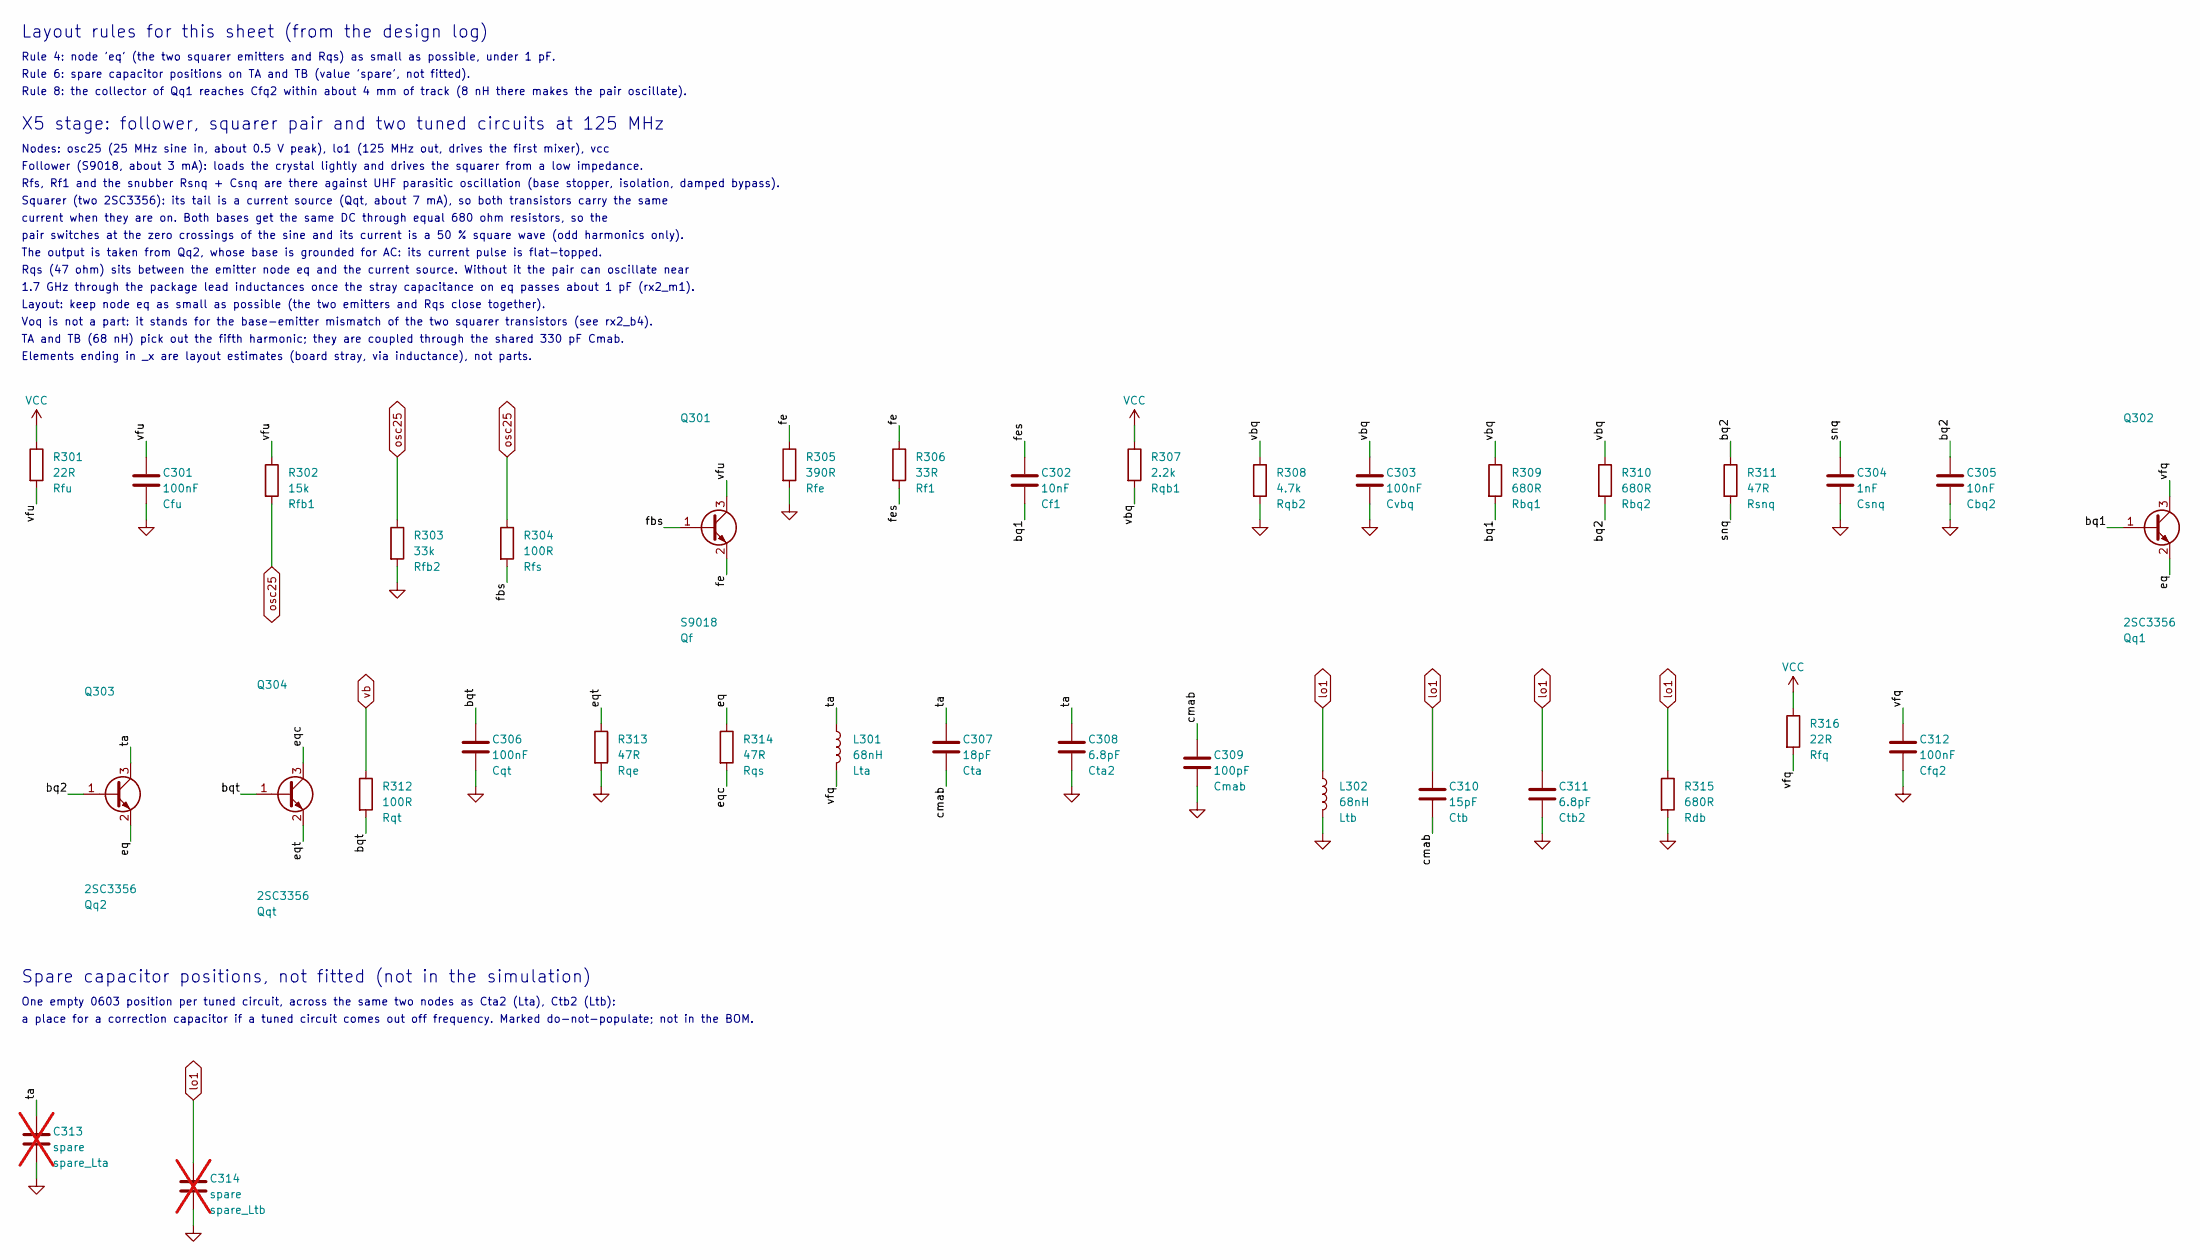
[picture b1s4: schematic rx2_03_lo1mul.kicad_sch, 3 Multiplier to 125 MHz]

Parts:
C301, C303, C306, C312: 100nF; C_0603_1608Metric; MPN CC0603KRX7R9BB104; LCSC C14663
C302, C305: 10nF; C_0603_1608Metric; MPN 0603B103K500NT; LCSC C57112
C304: 1nF; C_0603_1608Metric; MPN CL10B102KB8NNNC; LCSC C1588
C307: 18pF; C_0603_1608Metric; MPN CL10C180JB8NNNC; LCSC C1647
C308, C311: 6.8pF; C_0603_1608Metric; MPN 0603CG6R8C500NT; LCSC C1679
C309: 100pF; C_0603_1608Metric; MPN CL10C101JB8NNNC; LCSC C14858
C310: 15pF; C_0603_1608Metric; MPN CL10C150JB8NNNC; LCSC C1644
C313, C314: spare; C_0603_1608Metric; not fitted
L301, L302: 68nH; L_0603_LQW18A; MPN LQW18AN68NG00D; LCSC C86135
Q301: S9018; SOT-23; MPN S9018; LCSC C41375130
Q302, Q303, Q304: 2SC3356; SOT-23; MPN 2SC3356; LCSC C28646266
R301, R316: 22R; R_0603_1608Metric; MPN 0603WAF220JT5E; LCSC C23345
R302: 15k; R_0603_1608Metric; MPN 0603WAF1502T5E; LCSC C22809
R303: 33k; R_0603_1608Metric; MPN 0603WAF3302T5E; LCSC C4216
R304, R312: 100R; R_0603_1608Metric; MPN 0603WAF1000T5E; LCSC C22775
R305: 390R; R_0603_1608Metric; MPN 0603WAF3900T5E; LCSC C23151
R306: 33R; R_0603_1608Metric; MPN 0603WAF330JT5E; LCSC C23140
R307: 2.2k; R_0603_1608Metric; MPN 0603WAF2201T5E; LCSC C4190
R308: 4.7k; R_0603_1608Metric; MPN 0603WAF4701T5E; LCSC C23162
R309, R310, R315: 680R; R_0603_1608Metric; MPN 0603WAF6800T5E; LCSC C23228
R311, R313, R314: 47R; R_0603_1608Metric; MPN 0603WAF470JT5E; LCSC C23182

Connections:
/3 Multiplier to 125 MHz/bq1: C302.2, Q302.1 (B), R309.2
/3 Multiplier to 125 MHz/bq2: C305.1, Q303.1 (B), R310.2, R311.1
/3 Multiplier to 125 MHz/bqt: C306.1, Q304.1 (B), R312.2
/3 Multiplier to 125 MHz/cmab: C307.2, C309.1, C310.2
/3 Multiplier to 125 MHz/eq: Q302.2 (E), Q303.2 (E), R314.1
/3 Multiplier to 125 MHz/eqc: Q304.3 (C), R314.2
/3 Multiplier to 125 MHz/eqt: Q304.2 (E), R313.1
/3 Multiplier to 125 MHz/fbs: Q301.1 (B), R304.2
/3 Multiplier to 125 MHz/fe: Q301.2 (E), R305.1, R306.1
/3 Multiplier to 125 MHz/fes: C302.1, R306.2
/3 Multiplier to 125 MHz/snq: C304.1, R311.2
/3 Multiplier to 125 MHz/ta: C307.1, C308.1, C313.1, L301.1, Q303.3 (C)
/3 Multiplier to 125 MHz/vbq: C303.1, R307.2, R308.1, R309.1, R310.1
/3 Multiplier to 125 MHz/vfq: C312.1, L301.2, Q302.3 (C), R316.2
/3 Multiplier to 125 MHz/vfu: C301.1, Q301.3 (C), R301.2, R302.1
GND: C301.2, C303.2, C304.2, C305.2, C306.2, C308.2, C309.2, C311.2, C312.2, C313.2, C314.2, L302.2, R303.2, R305.2, R308.2, R313.2, R315.2; also elsewhere on the board
VCC: R301.1, R307.1, R316.1; also elsewhere on the board
lo1: C310.1, C311.1, C314.1, L302.1, R315.1; also elsewhere on the board
osc25: R302.2, R303.1, R304.1; also elsewhere on the board
vb: R312.1; also elsewhere on the board

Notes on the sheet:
Layout rules for this sheet (from the design log)
Rule 4: node 'eq' (the two squarer emitters and Rqs) as small as possible, under 1 pF.
Rule 6: spare capacitor positions on TA and TB (value 'spare', not fitted).
Rule 8: the collector of Qq1 reaches Cfq2 within about 4 mm of track (8 nH there makes the pair oscillate).
X5 stage: follower, squarer pair and two tuned circuits at 125 MHz
Nodes: osc25 (25 MHz sine in, about 0.5 V peak), lo1 (125 MHz out, drives the first mixer), vcc
Follower (S9018, about 3 mA): loads the crystal lightly and drives the squarer from a low impedance.
Rfs, Rf1 and the snubber Rsnq + Csnq are there against UHF parasitic oscillation (base stopper, isolation, damped bypass).
Squarer (two 2SC3356): its tail is a current source (Qqt, about 7 mA), so both transistors carry the same
current when they are on. Both bases get the same DC through equal 680 ohm resistors, so the
pair switches at the zero crossings of the sine and its current is a 50 % square wave (odd harmonics only).
The output is taken from Qq2, whose base is grounded for AC: its current pulse is flat-topped.
Rqs (47 ohm) sits between the emitter node eq and the current source. Without it the pair can oscillate near
1.7 GHz through the package lead inductances once the stray capacitance on eq passes about 1 pF (rx2_m1).
Layout: keep node eq as small as possible (the two emitters and Rqs close together).
Voq is not a part: it stands for the base-emitter mismatch of the two squarer transistors (see rx2_b4).
TA and TB (68 nH) pick out the fifth harmonic; they are coupled through the shared 330 pF Cmab.
Elements ending in _x are layout estimates (board stray, via inductance), not parts.
Spare capacitor positions, not fitted (not in the simulation)
One empty 0603 position per tuned circuit, across the same two nodes as Cta2 (Lta), Ctb2 (Ltb):
a place for a correction capacitor if a tuned circuit comes out off frequency. Marked do-not-populate; not in the BOM.
